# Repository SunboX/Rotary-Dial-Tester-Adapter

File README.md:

# Rotary Dial Tester Adapter

A small connector/adapter for testing vintage rotary dials (e.g., W48/W49) on a computer. It connects via DB9 RS232 (use an RS232-to-USB adapter) and provides both color-coded screw terminals (GE/GR/BR/WE) and a 4-pin connector for the dial wiring. This repository contains the KiCad project files.

## Overview
- DB9 RS232 interface for USB serial adapters
- Color-coded screw terminals (GE/GR/BR/WE)
- 4-pin connector for a cable harness
- Tested and working with: DIGITUS USB auf Seriell Adapter - RS232 Konverter - USB 2.0 Typ-C zu DSUB 9M - FTDI FT232RL Chipsatz - 1 m Anschlusskabel (https://www.amazon.de/dp/B07917RBBJ)

## Wooden base (CNC)
- Estlcam project: `adapter-wooden-base/Adapter_Base.E12`
- Estlcam is a CAM and CNC control program; offers inexpensive USB control hardware and easy control via gamepads, handwheel pendants, keyboard, and mouse.

## Required materials
- 18 mm wood for the base
- 4x brass wood screws, DIN 96 pan head, slotted, 3 mm x 8 mm
- 4x Keystone Electronics screw terminal 8191-3 (or 7770), M3
- 4x brass knurled screws, M3 x 6 x 9.5
- Adhesive dot set, 5 mm foil K020 (yellow, green, brown, white)
- 4x Wittkower solder terminal, 2.8 mm flat tab, straight, for PCB mounting
- 1x Wurth Elektronik 61800929321, D-SUB receptacle, 9-position, vertical solder

## Wiring
Use either the screw terminals or the 4-pin connector. The wiring diagram below shows the pin mapping.

### Pinout
- NSI (DCD) -> Yellow (GE) -> SUB-D pin 1
- RTS (common, high) -> Green (GR) + Brown (BR) tied together -> SUB-D pins 2 + 3
- NSA (NSA) -> White (WE) -> SUB-D pin 4
- NSR (DSR) is not connected on this board

NSR (DSR) is the dial’s off-normal/rest contact. It is closed at rest and opens when the dial starts, which can be used to detect start/end of dialing or to mute the speech path during dialing. For simple pulse counting, NSI (DCD) and optionally NSA (RI) are sufficient; if your dial needs NSR, you will need to rewire or modify the adapter.

Non-German rotary dials can be wired differently (e.g., 3-wire Ericsson or some US variants). If your dial needs NSR/DSR, you will need to rewire or modify the adapter, since only DCD/NSI and RI/NSA are routed.

## Web-based Rotary Dial Tester
Project: https://github.com/SunboX/Rotary-Dial-Tester (live: https://rotary-dial-tester.com/)

- Web app using the Web Serial API to read rotary dial pulses.
- Requirements: Chromium-based browser, served over `https://` or `http://localhost`, and a serial adapter that exposes modem status lines (DCD/DSR/RI).
- Signal mapping: nsi = DCD, nsr = DSR, nsa = RI; RTS is set high on connect.
- Usage: Connect COM, Start Test, then dial digits 2-0 (1 is too short for frequency measurement). The browser prompts for the port (no auto-detect).
- Debounce (EP): adds a wait time between DCD reads; higher values can reduce bounce but may affect measurements.
- Analysis: after 10 measurements of the same digit, the app shows runtime spread and pulse/pause tables.

## Photos

## License
This repository is licensed under PolyForm Noncommercial 1.0.0.
See `LICENSE` for the full license text and `NOTICE` for the
required notices that must accompany redistribution.

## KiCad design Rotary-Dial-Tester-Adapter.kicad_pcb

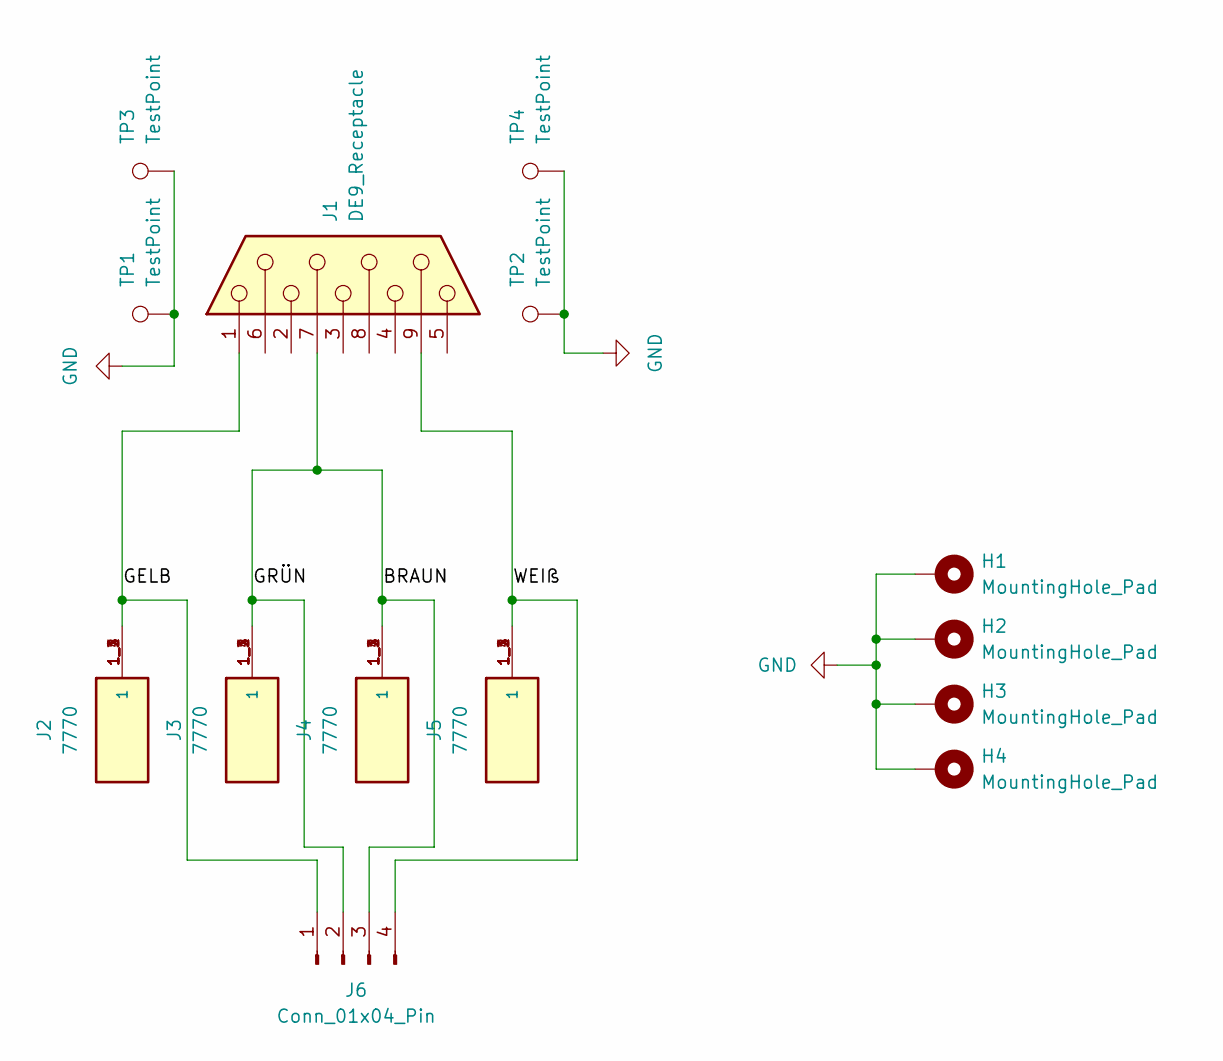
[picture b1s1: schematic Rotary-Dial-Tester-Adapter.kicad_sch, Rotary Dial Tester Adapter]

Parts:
H1, H2, H3, H4: MountingHole_Pad; MountingHole_3.2mm_M3_DIN965_Pad_TopBottom
J1: DE9_Receptacle; DSUB-9_Female_EdgeMount_P2.77mm
J2, J3, J4, J5: 7770; KEYSTONE_7770; PARTREV B
J6: Conn_01x04_Pin; PinSocket_1x04_P2.54mm_Vertical
TP1, TP2, TP3, TP4: TestPoint; TestPoint_Pad_3.0x3.0mm

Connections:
/BRAUN: J1.7, J3.1_1 (1), J3.1_2 (1), J3.1_3 (1), J3.1_4 (1), J4.1_1 (1), J4.1_2 (1), J4.1_3 (1), J4.1_4 (1), J6.2, J6.3
/GELB: J1.1, J2.1_1 (1), J2.1_2 (1), J2.1_3 (1), J2.1_4 (1), J6.1
/WEIß: J1.9, J5.1_1 (1), J5.1_2 (1), J5.1_3 (1), J5.1_4 (1), J6.4
GND: H1.1, H2.1, H3.1, H4.1, TP1.1, TP2.1, TP3.1, TP4.1

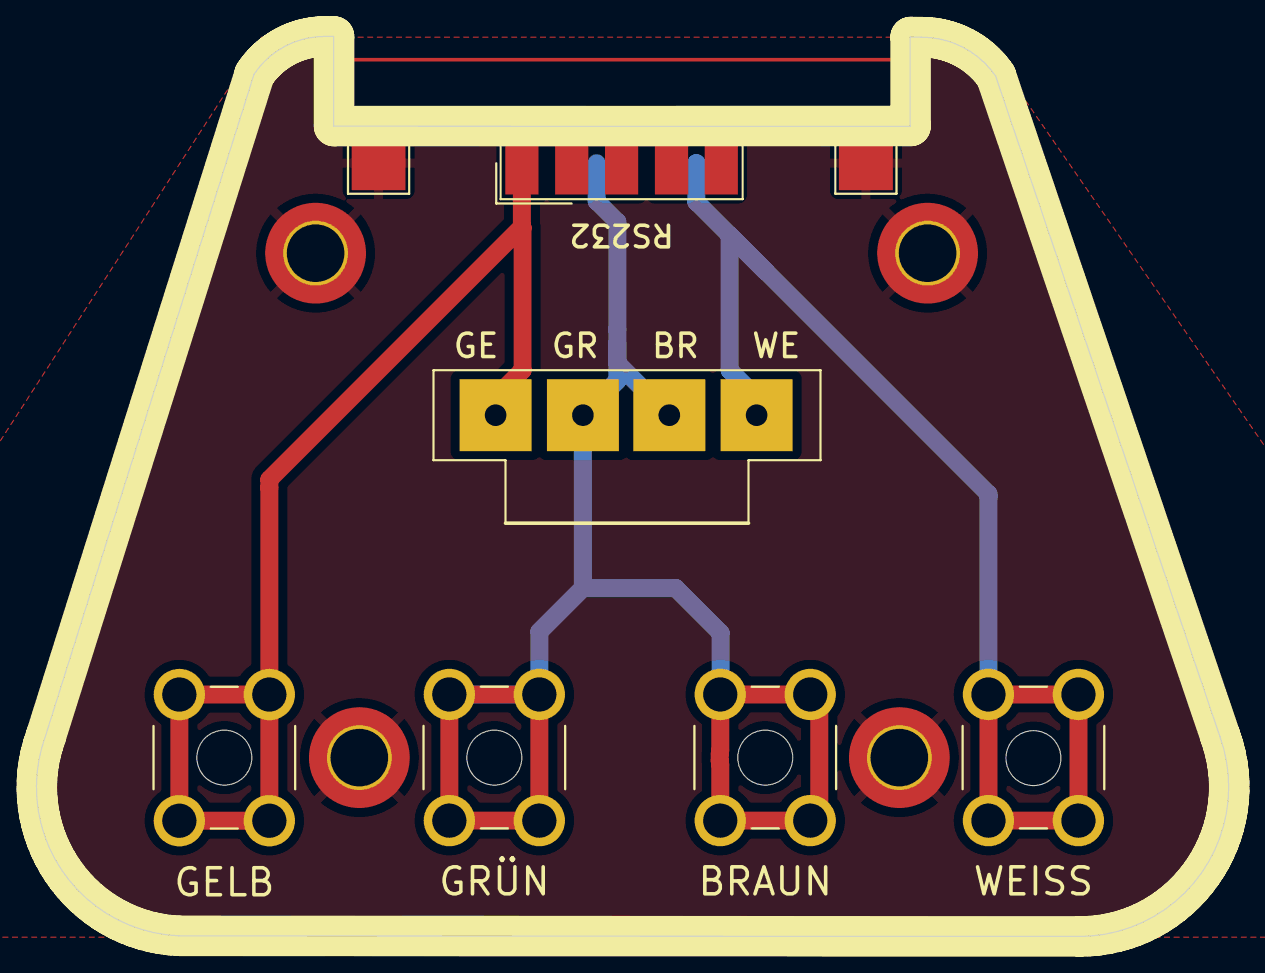
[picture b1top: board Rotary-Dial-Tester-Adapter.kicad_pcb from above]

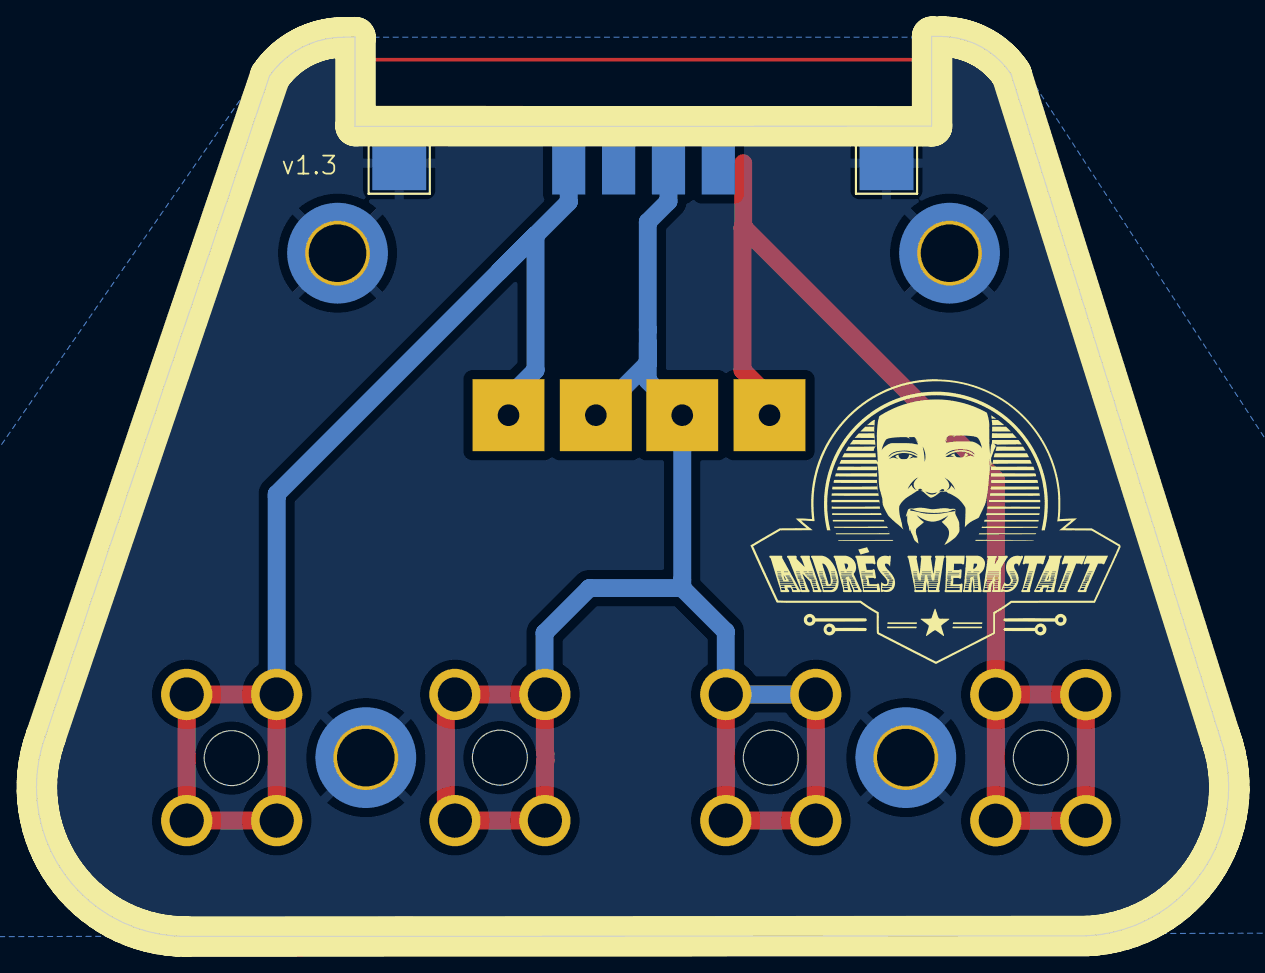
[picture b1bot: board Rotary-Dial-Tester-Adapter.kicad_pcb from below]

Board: 2 copper layers, 66.2 x 50.0 mm, 14 parts (2 on the bottom side), 4 nets.

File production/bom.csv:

Designator,Footprint,Quantity,Value,LCSC Part #
J1,DSUB-9_Female_EdgeMount_P2.77mm,1,DE9_Receptacle,
"J2, J3, J4, J5",KEYSTONE_7770,4,7770,
J6,PinSocket_1x04_P2.54mm_Vertical,1,Conn_01x04_Pin,
"TP1, TP2, TP3, TP4",TestPoint_Pad_3.0x3.0mm,4,TestPoint,

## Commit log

2025-12-28 Ignores backup directory
    Prevents the backup directory from being tracked by Git.
    This avoids accidentally committing sensitive or irrelevant backup files.
2026-01-12 deleted old project files
2026-01-12 Migrates project files to graphics/ and renames
    Moves graphic files to the dedicated graphics/ directory.
    Renames main project files for better clarity and consistency,
    reflecting the adapter's purpose.
    Adds a complete project README with wiring diagram
    and project context.
    Adds example photos of wiring and device assembly.
2026-01-12 Adds project license and metadata
    Adds a "Permission Required License" and copyright notice.
    Updates the schematic and PCB files to include a title block with project metadata and license information.
    This ensures proper attribution and clarifies usage restrictions.
2026-01-12 Adds initial fabrication toolkit files
    Adds necessary files for the fabrication toolkit,
    including options, BOM, designators, netlist,
    component positions, and production archives.
2026-01-12 Adds tested USB serial adapter
    Documents a tested and working USB to serial adapter model.
    This allows users to quickly find a compatible adapter for their rotary dial testing setup.
2026-01-13 Increases solder mask clearance
    Increases the solder mask to copper clearance value.
    This adjustment improves manufacturability by providing a small buffer between the solder mask and copper features, reducing the risk of solder mask encroachment.
2026-01-13 Clarifies project purpose in README
    Adds a sentence to the README to explicitly state that the
    repository contains the KiCad project files for the rotary dial tester.
2026-01-13 Adds CNC project for wooden base
    Adds Estlcam project files to create a wooden base for the
    adapter, which can be used with CNC machines.
    Provides project and CAM data with gcode for Adapter Base.
2026-01-13 Enhances README with additional details on Estlcam control options and required materials for the wooden base
2026-01-13 Updates required materials in README to correct screw terminal part number
2026-01-13 Clarifies required materials in README by specifying alternative part number for screw terminal
2026-01-15 Adds detailed pinout information and wiring notes for rotary dials in README
2026-03-22 Updates license information to PolyForm Noncommercial 1.0.0 and adds NOTICE file with required notices

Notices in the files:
Rotary-Dial-Tester-Adapter.kicad_pcb:
Copyright (c) 2026 Andre Fiedler. All rights reserved.
Use requires written permission; see LICENSE.
